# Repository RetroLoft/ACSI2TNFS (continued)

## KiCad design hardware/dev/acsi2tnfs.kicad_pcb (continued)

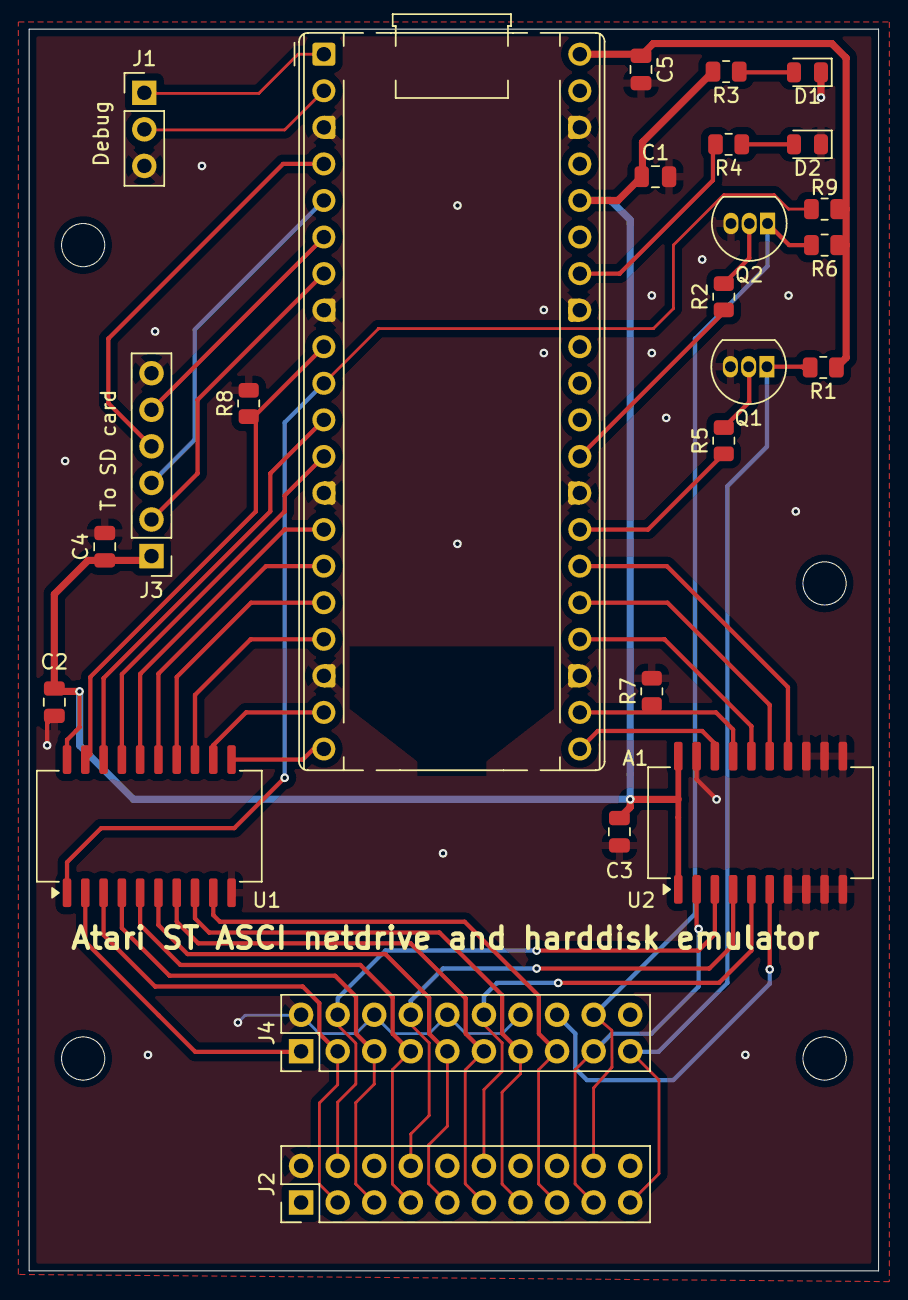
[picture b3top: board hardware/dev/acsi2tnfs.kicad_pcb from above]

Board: 2 copper layers, 59.0 x 86.2 mm, 25 parts (0 on the bottom side), 46 nets.
